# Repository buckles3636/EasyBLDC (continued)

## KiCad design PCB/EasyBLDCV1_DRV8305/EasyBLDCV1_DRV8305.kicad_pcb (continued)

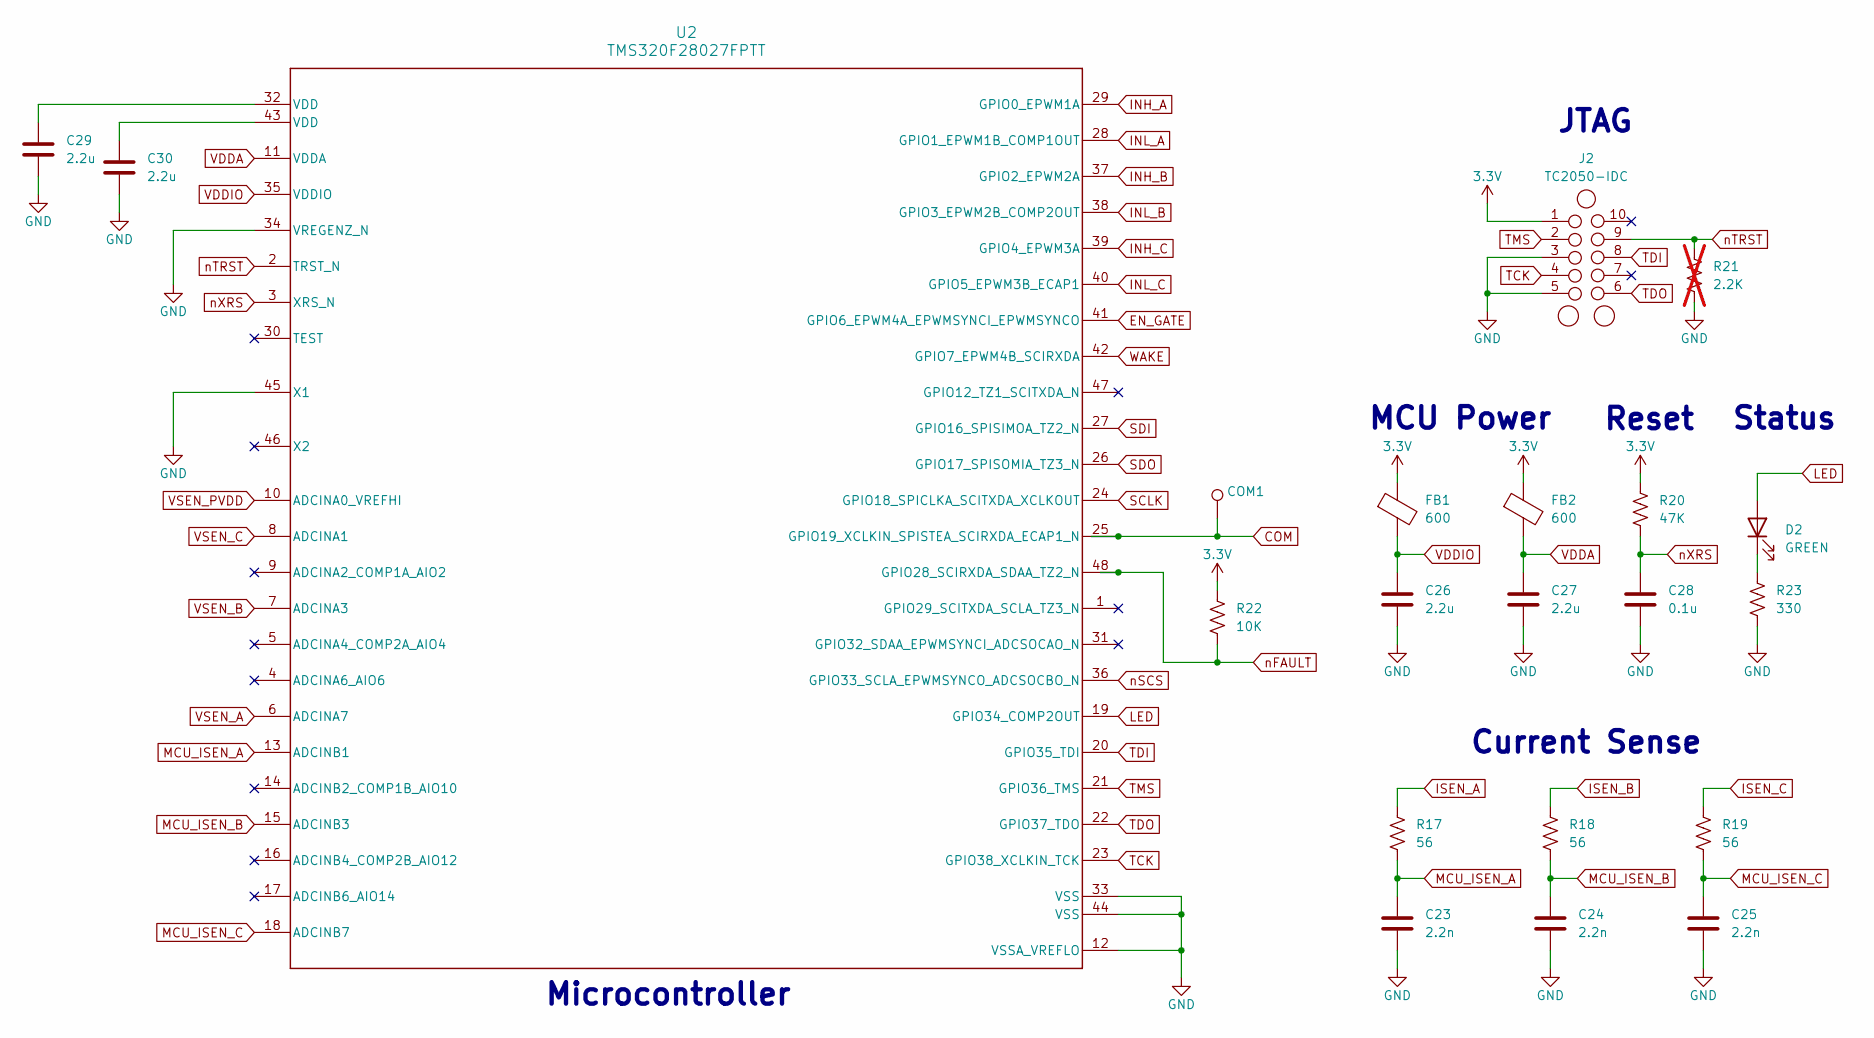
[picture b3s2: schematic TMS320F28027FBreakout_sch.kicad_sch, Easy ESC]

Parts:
C23, C24, C25: 2.2n; C_0402_1005Metric
C26, C27, C29, C30: 2.2u; C_0603_1608Metric
C28: 0.1u; C_0402_1005Metric
COM1: TestPoint; TestPoint_Pad_D2.0mm
D2: GREEN; LED_0805_2012Metric
FB1, FB2: 600; L_0603_1608Metric
J2: TC2050-IDC; Tag-Connect_TC2050-IDC-NL_2x05_P1.27mm_Vertical
R17, R18, R19: 56; R_0402_1005Metric
R20: 47K; R_0603_1608Metric
R21: 2.2K; R_0603_1608Metric; not fitted
R22: 10K; R_0603_1608Metric
R23: 330; R_0603_1608Metric
U2: TMS320F28027FPTT; PT0048A_N

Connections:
3.3V: FB1.1, FB2.1, J2.1, R20.1, R22.1; also elsewhere on the board
COM: COM1.1, U2.25 (GPIO19_XCLKIN_SPISTEA_SCIRXDA_ECAP1_N); also elsewhere on the board
EN_GATE: U2.41 (GPIO6_EPWM4A_EPWMSYNCI_EPWMSYNCO); also elsewhere on the board
GND: C23.2, C24.2, C25.2, C26.2, C27.2, C28.2, C29.2, C30.2, J2.3, J2.5, R21.2, R23.2, U2.12 (VSSA_VREFLO), U2.33 (VSS), U2.34 (VREGENZ_N), U2.44 (VSS), U2.45 (X1); also elsewhere on the board
INH_A: U2.29 (GPIO0_EPWM1A); also elsewhere on the board
INH_B: U2.37 (GPIO2_EPWM2A); also elsewhere on the board
INH_C: U2.39 (GPIO4_EPWM3A); also elsewhere on the board
INL_A: U2.28 (GPIO1_EPWM1B_COMP1OUT); also elsewhere on the board
INL_B: U2.38 (GPIO3_EPWM2B_COMP2OUT); also elsewhere on the board
INL_C: U2.40 (GPIO5_EPWM3B_ECAP1); also elsewhere on the board
ISEN_A: R17.1; also elsewhere on the board
ISEN_B: R18.1; also elsewhere on the board
ISEN_C: R19.1; also elsewhere on the board
LED: D2.2 (A), U2.19 (GPIO34_COMP2OUT)
MCU_ISEN_A: C23.1, R17.2, U2.13 (ADCINB1)
MCU_ISEN_B: C24.1, R18.2, U2.15 (ADCINB3)
MCU_ISEN_C: C25.1, R19.2, U2.18 (ADCINB7)
unnamed: C29.1, U2.32 (VDD)
unnamed: C30.1, U2.43 (VDD)
unnamed: D2.1 (K), R23.1
SCLK: U2.24 (GPIO18_SPICLKA_SCITXDA_XCLKOUT); also elsewhere on the board
SDI: U2.27 (GPIO16_SPISIMOA_TZ2_N); also elsewhere on the board
SDO: U2.26 (GPIO17_SPISOMIA_TZ3_N); also elsewhere on the board
TCK: J2.4, U2.23 (GPIO38_XCLKIN_TCK)
TDI: J2.8, U2.20 (GPIO35_TDI)
TDO: J2.6, U2.22 (GPIO37_TDO)
TMS: J2.2, U2.21 (GPIO36_TMS)
VDDA: C27.1, FB2.2, U2.11 (VDDA)
VDDIO: C26.1, FB1.2, U2.35 (VDDIO)
VSEN_A: U2.6 (ADCINA7); also elsewhere on the board
VSEN_B: U2.7 (ADCINA3); also elsewhere on the board
VSEN_C: U2.8 (ADCINA1); also elsewhere on the board
VSEN_PVDD: U2.10 (ADCINA0_VREFHI); also elsewhere on the board
WAKE: U2.42 (GPIO7_EPWM4B_SCIRXDA); also elsewhere on the board
nFAULT: R22.2, U2.48 (GPIO28_SCIRXDA_SDAA_TZ2_N); also elsewhere on the board
nSCS: U2.36 (GPIO33_SCLA_EPWMSYNCO_ADCSOCBO_N); also elsewhere on the board
nTRST: J2.9, R21.1, U2.2 (TRST_N)
nXRS: C28.1, R20.2, U2.3 (XRS_N)

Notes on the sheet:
MCU Power
Current Sense
Reset
Status
Microcontroller
JTAG

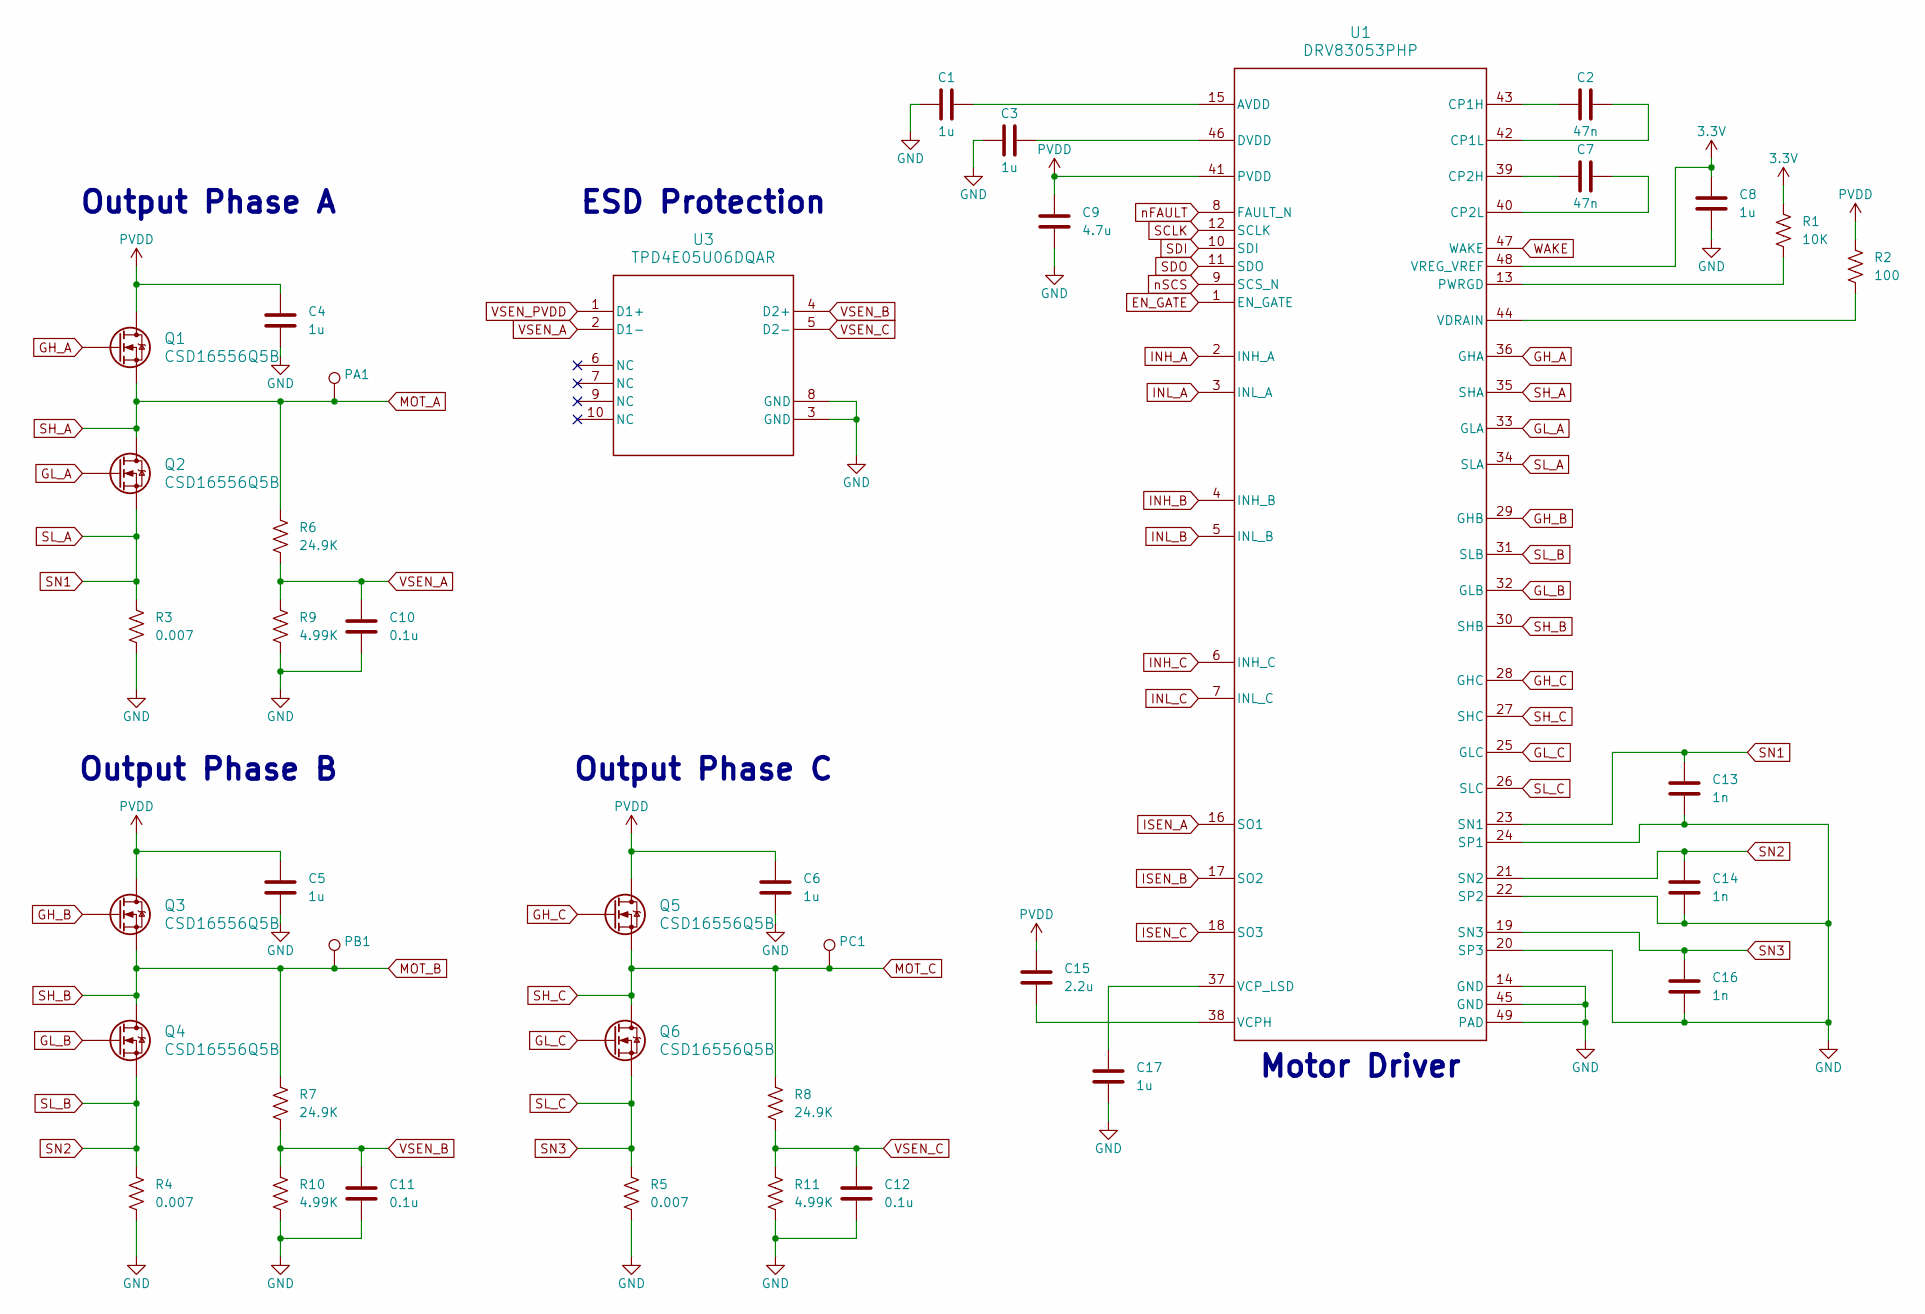
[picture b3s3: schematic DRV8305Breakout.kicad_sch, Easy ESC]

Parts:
C1, C3, C4, C5, C6, C8, C17: 1u; C_0603_1608Metric
C2, C7: 47n; C_0603_1608Metric
C9: 4.7u; C_0603_1608Metric
C10, C11, C12: 0.1u; C_0402_1005Metric
C13, C14, C16: 1n; C_0402_1005Metric
C15: 2.2u; C_0603_1608Metric
PA1: TestPoint; TestPoint_Pad_D2.0mm
PB1: TestPoint; TestPoint_Pad_D2.0mm
PC1: TestPoint; TestPoint_Pad_D2.0mm
Q1, Q2, Q3, Q4, Q5, Q6: CSD16556Q5B; DNK0008A
R1: 10K; Fuse_0603_1608Metric
R2: 100; Fuse_0603_1608Metric
R3, R4, R5: 0.007; R_2512_6332Metric
R6, R7, R8: 24.9K; R_0603_1608Metric
R9, R10, R11: 4.99K; R_0402_1005Metric
U1: DRV83053PHP; PHP0048G_N
U3: TPD4E05U06DQAR; DQA0010A

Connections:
3.3V: C8.1, R1.1, U1.48 (VREG_VREF); also elsewhere on the board
EN_GATE: U1.1 (EN_GATE); also elsewhere on the board
GH_A: Q1.4 (G), U1.36 (GHA)
GH_B: Q3.4 (G), U1.29 (GHB)
GH_C: Q5.4 (G), U1.28 (GHC)
GL_A: Q2.4 (G), U1.33 (GLA)
GL_B: Q4.4 (G), U1.32 (GLB)
GL_C: Q6.4 (G), U1.25 (GLC)
GND: C1.1, C3.1, C4.2, C5.2, C6.2, C8.2, C9.2, C10.2, C11.2, C12.2, C13.2, C14.2, C16.2, C17.2, R3.2, R4.2, R5.2, R9.2, R10.2, R11.2, U1.14 (GND), U1.20 (SP3), U1.22 (SP2), U1.24 (SP1), U1.45 (GND), U1.49 (PAD), U3.3 (GND), U3.8 (GND); also elsewhere on the board
INH_A: U1.2 (INH_A); also elsewhere on the board
INH_B: U1.4 (INH_B); also elsewhere on the board
INH_C: U1.6 (INH_C); also elsewhere on the board
INL_A: U1.3 (INL_A); also elsewhere on the board
INL_B: U1.5 (INL_B); also elsewhere on the board
INL_C: U1.7 (INL_C); also elsewhere on the board
ISEN_A: U1.16 (SO1); also elsewhere on the board
ISEN_B: U1.17 (SO2); also elsewhere on the board
ISEN_C: U1.18 (SO3); also elsewhere on the board
MOT_A: PA1.1, Q1.1 (S), Q1.2 (S), Q1.3 (S), Q2.5 (D), Q2.6 (D), Q2.7 (D), Q2.8 (D), R6.1, U1.35 (SHA); also elsewhere on the board
MOT_B: PB1.1, Q3.1 (S), Q3.2 (S), Q3.3 (S), Q4.5 (D), Q4.6 (D), Q4.7 (D), Q4.8 (D), R7.1, U1.30 (SHB); also elsewhere on the board
MOT_C: PC1.1, Q5.1 (S), Q5.2 (S), Q5.3 (S), Q6.5 (D), Q6.6 (D), Q6.7 (D), Q6.8 (D), R8.1, U1.27 (SHC); also elsewhere on the board
unnamed: C1.2, U1.15 (AVDD)
unnamed: C2.1, U1.43 (CP1H)
unnamed: C2.2, U1.42 (CP1L)
unnamed: C7.1, U1.39 (CP2H)
unnamed: C7.2, U1.40 (CP2L)
unnamed: C3.2, U1.46 (DVDD)
unnamed: R1.2, U1.13 (PWRGD)
unnamed: C15.2, U1.38 (VCPH)
unnamed: C17.1, U1.37 (VCP_LSD)
unnamed: R2.2, U1.44 (VDRAIN)
PVDD: C4.1, C5.1, C6.1, C9.1, C15.1, Q1.5 (D), Q1.6 (D), Q1.7 (D), Q1.8 (D), Q3.5 (D), Q3.6 (D), Q3.7 (D), Q3.8 (D), Q5.5 (D), Q5.6 (D), Q5.7 (D), Q5.8 (D), R2.1, U1.41 (PVDD); also elsewhere on the board
SCLK: U1.12 (SCLK); also elsewhere on the board
SDI: U1.10 (SDI); also elsewhere on the board
SDO: U1.11 (SDO); also elsewhere on the board
SL_A: C13.1, Q2.1 (S), Q2.2 (S), Q2.3 (S), R3.1, U1.23 (SN1), U1.34 (SLA)
SL_B: C14.1, Q4.1 (S), Q4.2 (S), Q4.3 (S), R4.1, U1.21 (SN2), U1.31 (SLB)
SL_C: C16.1, Q6.1 (S), Q6.2 (S), Q6.3 (S), R5.1, U1.19 (SN3), U1.26 (SLC)
VSEN_A: C10.1, R6.2, R9.1, U3.2 (D1-); also elsewhere on the board
VSEN_B: C11.1, R7.2, R10.1, U3.4 (D2+); also elsewhere on the board
VSEN_C: C12.1, R8.2, R11.1, U3.5 (D2-); also elsewhere on the board
VSEN_PVDD: U3.1 (D1+); also elsewhere on the board
WAKE: U1.47 (WAKE); also elsewhere on the board
nFAULT: U1.8 (FAULT_N); also elsewhere on the board
nSCS: U1.9 (SCS_N); also elsewhere on the board

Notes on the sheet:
Output Phase A
ESD Protection
Output Phase C
Motor Driver
Output Phase B

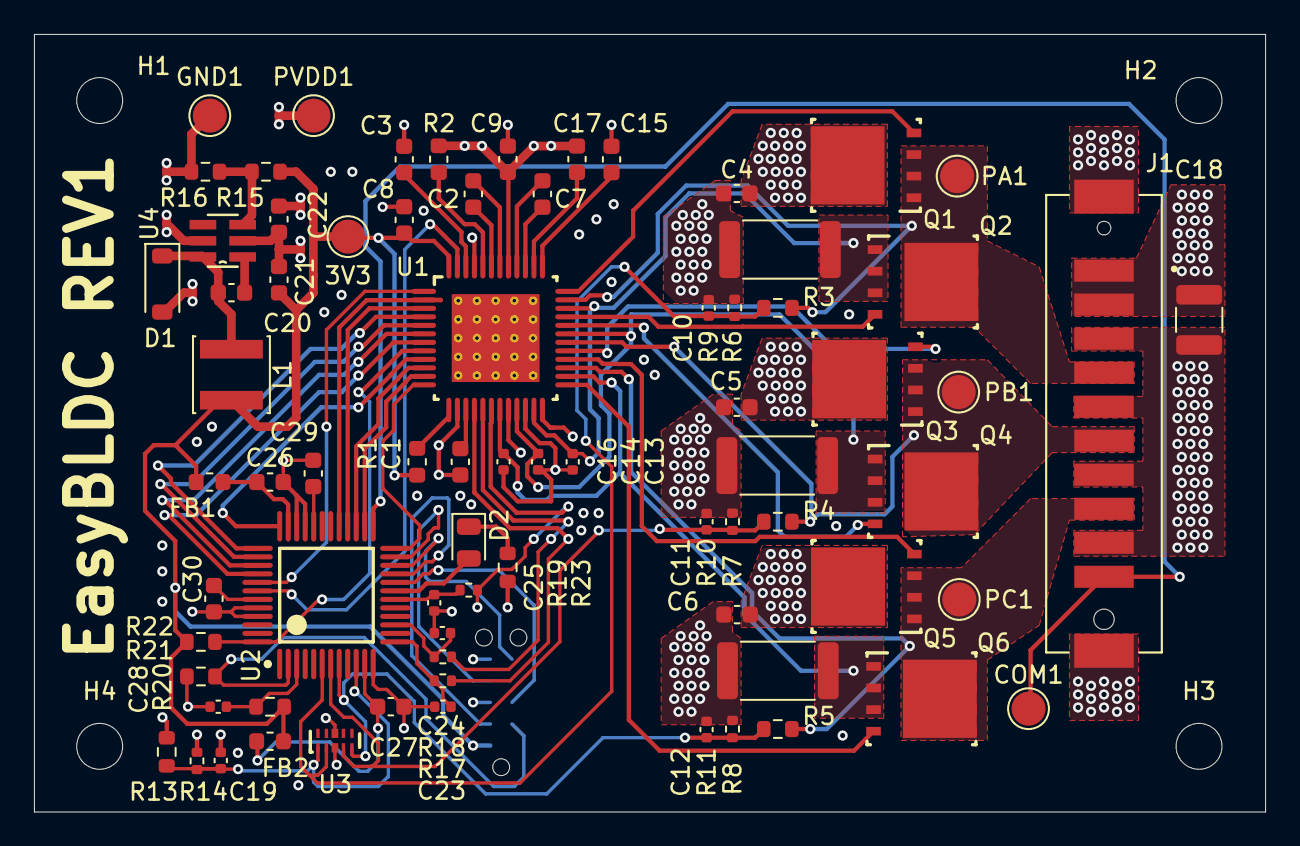
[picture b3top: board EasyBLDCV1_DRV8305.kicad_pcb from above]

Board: 4 copper layers, 72.4 x 45.7 mm, 80 parts (1 on the bottom side), 64 nets.

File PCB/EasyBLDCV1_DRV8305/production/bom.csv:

Designator,Footprint,Quantity,Value,LCSC Part #
"C1, C17, C22, C3, C4, C5, C6, C8",0603,8,1u,
"C10, C11, C12, C19, C28",0402,5,0.1u,
"C13, C14, C16",0402,3,1n,
"C15, C26, C27, C29, C30",0603,5,2.2u,
C18,1210,1,10u,
"C2, C7",0603,2,47n,
C20,0603,1,0.33u,
C21,0603,1,22u,
"C23, C24, C25",0402,3,2.2n,
C9,0603,1,4.7u,
D1,D_SOD-123,1,D_Schottky,
D2,0805,1,GREEN,
"FB1, FB2",0603,2,600,
J1,AMPHENOL_10159560-A00221RLF,1,10159560-A00221RLF,
L1,L_Changjiang_FNR4020S,1,SD53-120-R,
"Q1, Q2, Q3, Q4, Q5, Q6",DNK0008A,6,CSD16556Q5B,
"R1, R22",0603,2,10K,
"R10, R11, R14, R9",0402,4,4.99K,
"R13, R6, R7, R8",0603,4,24.9K,
R15,0603,1,68k,
R16,0603,1,20k,
"R17, R18, R19",0402,3,56,
R2,0603,1,100,
R20,0603,1,47K,
R23,0603,1,330,
"R3, R4, R5",2512,3,0.007,
U1,PHP0048G_N,1,DRV83053PHP,
U2,PT0048A_N,1,TMS320F28027FPTT,
U3,DQA0010A,1,TPD4E05U06DQAR,
U4,DDC0006A,1,LMR16006XDDCR,

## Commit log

2024-08-02 Started V1 Schematics
2024-08-06 Finished REV1 Schematic Awaiting Review
2024-08-06 Updated Some Errors in Schematic
2024-08-06 Fixed issue with fet symbol and started layout
2024-08-07 Started Layout
2024-08-13 Fixed Naming Scheme
2024-08-13 Updated Schematic With Missing Footprints
2024-08-13 Progress on MCU Breakout
2024-08-13 Continued work on layout
2024-08-13 Started DRV Breakout
2024-08-13 Continued work on drv8305 breakout
2024-08-14 Initial Layout For Mosfets
2024-08-14 Finished Mosfet Layout
2024-08-14 Started layout between drv and fets
2024-08-14 Started Connecting Microcontroller
2024-08-15 Continued layout work
2024-08-15 Finished Initial Layout
2024-08-15 Fixed ref des
2024-08-15 Fixed More DRC started final layout
2024-08-15 Updated PCB Graphics and Layout
2024-08-15 Created Logos
2024-08-16 Updated Inductor and excluded tps from BOM
2024-08-25 Colored main connector
2024-09-04 Fixed errors with silkscreen overlaping vias. Generated final gerbers.
2024-09-04 Ran Final DRC Check
2024-09-06 Changed Step Color File
2024-09-06 Changed main connector pinout to improve signal integrity
2024-09-06 Fixed Silkscreen DRC Errors
2024-09-06 Generated V1.0 final production files
2024-09-07 JTAG Connector Changed
2024-10-19 Created V2 Project Files
2024-10-20 Deleted V1 Relics, redid power stage
2024-10-23 Deleted Parts from v1
2024-10-24 Broke-out mcf8329
2024-10-24 Added comments to schematic
2024-10-25 Finished schematic
2024-10-25 Assigned footprints, created bom
2024-10-26 Started component layout
2024-10-26 Redid Power Fills
2024-10-26 More work on layout
2024-10-30 Added footprints for ESC and additional connectors
2024-10-30 Adjusted power traces
2024-11-01 Finished Silscreen
2024-11-01 Changed Stackup
2024-11-03 Finished V2
2024-11-15 Updated BOM
2024-12-08 First Configuration File
    Motor spins but needs additional tuning
2024-12-23 Updated Step File
2025-01-15 Added Components for Version 3
2025-01-20 Got stm dev board running
2025-01-21 Added footprints and began schematic for new gate drive
2025-01-28 Worked on gate drive schematic
2025-02-22 Created V4 Project
2025-02-23 Finished Schematic Assigned Footprints
2025-02-23 More layout progress
2025-02-23 Layout almost final
2025-02-23 Design finished, ready for review
2025-02-24 Fixed DRC Errors. Ready for review
2025-02-24 Updated Board According to Dirk Kaisers Review
2025-03-04 Finished v3
2025-03-25 updated some shit idk
2025-03-26 Changed out 0201 resistors, production version
